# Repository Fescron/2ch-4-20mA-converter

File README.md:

# 2ch-4-20mA-converter

<br/>

This board converts two *4 - 20 mA* signals to a voltage using a `LMP8640` *Current Shunt Monitor* from *Texas Instruments*. To provide power to the *4 - 20 mA* sensors a `TEC2-0913` 2W 15V Isolated DC-DC converter is used from *Traco Power*. Quick-connect terminals from *Phoenix Contact* are also used.

To allow for extensive testing three separate GND nets/planes and a lot of test points are used. They can be connected together using jumpers if necessary. The power supply can also be disabled and fully disconnected from the sensors using a jumper as well (wich can also be used to measure the in-line current given to the whole sensor circuit).

- Click [here](hardware/2ch-4-20mA/2ch-4-20mA.pdf) to go to the **schematic**.

<br/>

 &nbsp; &nbsp; &nbsp; &nbsp; &nbsp; 

<br/>

## LMP8640 vs INA196

A lot of designs still use the `INA196` *Current Shunt Monitor* from *Texas Instruments*. In the picture below is a comparison between the `LMP8640` and the `INA196`. No real disadvantage was found to not use the `LMP8640`.

<br/>

<br/>

## BOM

| Component    | Value                | Footprint     | Other                                       | Ordering                                                                                                                                    |
| ------------ | -------------------- | ------------- | ------------------------------------------- | ------------------------------------------------------------------------------------------------------------------------------------------- |
| U1, U2       | LMP8640              | SOT-23-Thin-6 | Texas Instruments Current Shunt Monitor     | [Mouser.be](https://www.mouser.be/ProductDetail/Texas-Instruments/LMP8640MK-T-NOPB?qs=sGAEpiMZZMvEn2pkGav3bPb6jlX9oNVbBBSIeXfzDzM%3D)                     |
| U3           | TEC2-0913            | SIP-8         | Traco Power 2W 15V Isolated DC-DC converter | [Mouser.be](https://www.mouser.be/ProductDetail/TRACO-Power/TEC-2-0913?qs=sGAEpiMZZMvGsmoEFRKS8Koqt8Pjkl39l4aaKfuLyMgVYp%252Bicpvd3A%3D%3D) |
| C1, C2       | 100 nF = 0,1 µF      | 0805          | X7R, 16V, 10%                               | [Mouser.be](https://www.mouser.be/ProductDetail/Yageo/CC0805KRX7R7BB104?qs=sGAEpiMZZMs0AnBnWHyRQMMzfhmH8IQX2eB5GrOHrwc%3D)                  |
| R1, R2       | 6,2 Ω                | 0805          | 0,1%                                        | [Mouser.be](https://www.mouser.be/ProductDetail/TE-Connectivity-Neohm/CPF0805B6R2E1?qs=sGAEpiMZZMu61qfTUdNhGxAfPTOoMd3Mys3VDWDGxkc%3D)      |
| R1, R2 (alt) | 4,99 Ω               | 0805          | 0,1%                                        | [Mouser.be](https://www.mouser.be/ProductDetail/TE-Connectivity-Neohm/CPF0805B4R99E1?qs=sGAEpiMZZMu61qfTUdNhGxAfPTOoMd3MWO8ubRKmtsI%3D)     |
| J1, J2       | PTSA_1,5/_2-3,5-Z_BK | Pitch: 3,5 mm | 2 contacts @ 45° (20-16 AWG), 250V 2A       | [Mouser.be](https://www.mouser.be/ProductDetail/Phoenix-Contact/1751765?qs=sGAEpiMZZMvZTcaMAxB2AOnzhHajZlLEGRULH%2FxUGnk%3D)                |

<br/>

## UPDATE 03/2020 - 1 CH board without power supply

To better conduct tests with the `LMP8640` chip a simple 1-CH board was layed out without a power supply and etched on a single sided board.

- Click [here](hardware/1ch-4-20mA/Plots/1ch-4-20mA.pdf) to go to the **schematic**.
- Click [here](hardware/1ch-4-20mA/Plots/1ch-4-20mA-F_Cu.pdf) to go to the **board layout** (mirrored).

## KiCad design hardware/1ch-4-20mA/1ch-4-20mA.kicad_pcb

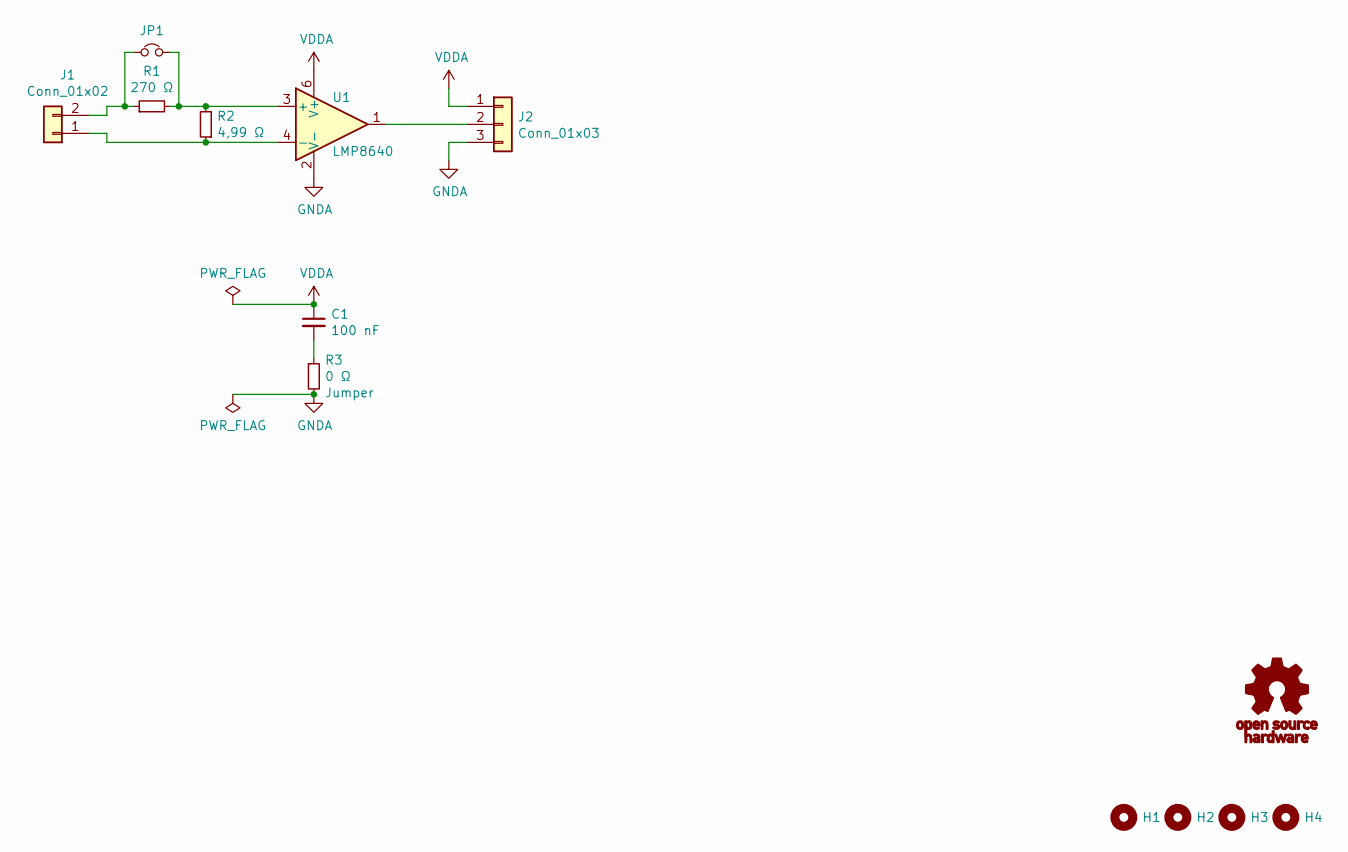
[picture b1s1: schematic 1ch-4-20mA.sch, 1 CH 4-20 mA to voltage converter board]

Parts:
C1: 100 nF; C_0805_2012Metric_Pad1.15x1.40mm_HandSolder
G1: Symbol_OSHW-Logo_11.4x12mm; OSHW-Logo_5.7x6mm_SolderMask
H1, H2, H3, H4: MountingHole; MountingHole_3.2mm_M3
J1: Conn_01x02; PhoenixContact_PTSA_1,5_2-G-3,5_1x02_P3.50mm_Angled
J2: Conn_01x03; PinHeader_1x03_P2.54mm_Vertical_SMD_Pin1Right
JP1: Jumper_NC_Small; PinHeader_1x02_P2.54mm_Vertical_SMD_Pin1Left
R1: 270 Ω; R_0805_2012Metric_Pad1.15x1.40mm_HandSolder
R2: 4,99 Ω; R_0805_2012Metric_Pad1.15x1.40mm_HandSolder
R3: 0 Ω; R_0805_2012Metric_Pad1.15x1.40mm_HandSolder
U1: LMP8640; SOT-23-6_Handsoldering

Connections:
GNDA: J2.3, R3.2, U1.2 (V-)
unnamed: C1.2, R3.1
unnamed: J1.1, R2.1, U1.4 (-)
unnamed: J1.2, JP1.1, R1.1
unnamed: J2.2, U1.1
unnamed: JP1.2, R1.2, R2.2, U1.3 (+)
VDDA: C1.1, J2.1, U1.6 (V+)

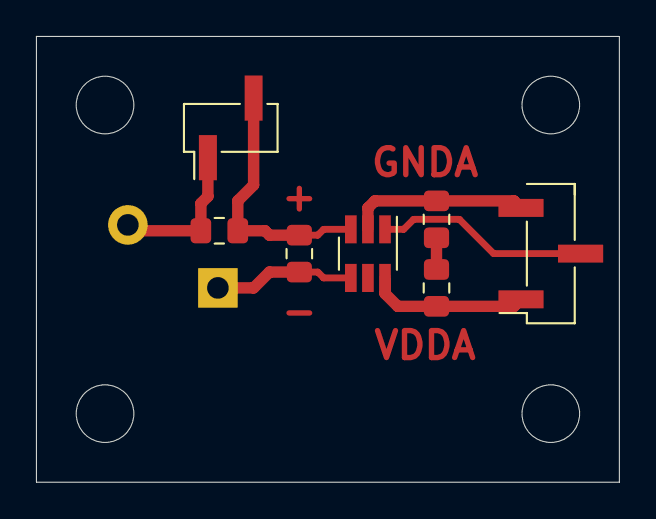
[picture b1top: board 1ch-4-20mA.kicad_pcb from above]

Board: 2 copper layers, 32.4 x 24.8 mm, 13 parts (1 on the bottom side), 7 nets.

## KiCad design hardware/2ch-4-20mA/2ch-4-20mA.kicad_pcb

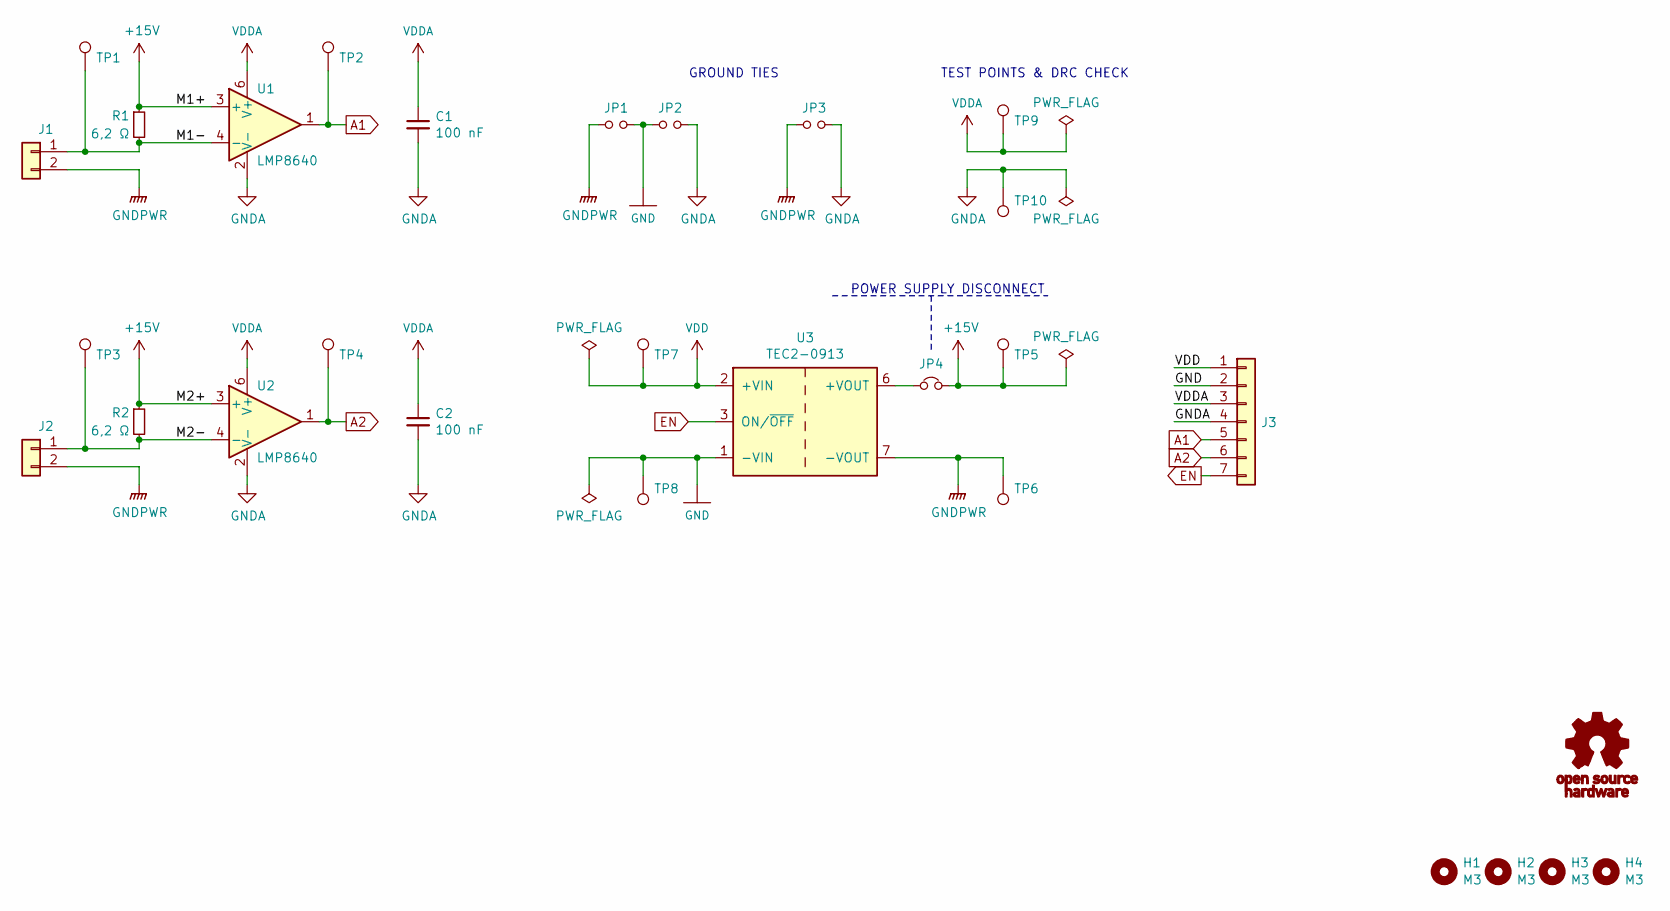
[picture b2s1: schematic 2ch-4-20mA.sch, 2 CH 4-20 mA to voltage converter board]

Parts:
C1, C2: 100 nF; C_0805_2012Metric_Pad1.15x1.40mm_HandSolder
G1: OSHW-EEVBLOG-SPFMDBC-10mm; OSHW-Logo_5.7x6mm_SolderMask
H1, H2, H3, H4: M3; MountingHole_3.2mm_M3
J1, J2: Conn_01x02; PhoenixContact_PTSA_1,5_2-G-3,5_1x02_P3.50mm_Angled
J3: Conn_01x07; PinHeader_1x07_P2.54mm_Vertical
JP1, JP2, JP3: Jumper_NO_Small; PinHeader_1x02_P2.54mm_Vertical
JP4: Jumper_NC_Small; PinHeader_1x02_P2.54mm_Vertical
R1, R2: 6,2 Ω; R_0805_2012Metric_Pad1.15x1.40mm_HandSolder
TP1, TP2, TP3, TP4, TP5, TP6, TP7, TP8, TP9, TP10: TestPoint; TestPoint_THTPad_D2.0mm_Drill1.0mm
U1, U2: LMP8640; SOT-23-6_Handsoldering
U3: TEC2-0913; SIP-8 TEC2-0913

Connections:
+15V: JP4.2, R1.1, R2.1, TP5.1, U1.3 (+), U2.3 (+)
/M1-: J1.1, R1.2, TP1.1, U1.4 (-)
/M2-: J2.1, R2.2, TP3.1, U2.4 (-)
A1: J3.5, TP2.1, U1.1
A2: J3.6, TP4.1, U2.1
EN: J3.7, U3.3 (ON/~OFF)
GND: J3.2, JP1.2, JP2.1, TP8.1, U3.1 (-VIN)
GNDA: C1.2, C2.2, J3.4, JP2.2, JP3.2, TP10.1, U1.2 (V-), U2.2 (V-)
GNDPWR: J1.2, J2.2, JP1.1, JP3.1, TP6.1, U3.7 (-VOUT)
unnamed: JP4.1, U3.6 (+VOUT)
VDD: J3.1, TP7.1, U3.2 (+VIN)
VDDA: C1.1, C2.1, J3.3, TP9.1, U1.6 (V+), U2.6 (V+)

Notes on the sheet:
GROUND TIES
TEST POINTS & DRC CHECK
POWER SUPPLY DISCONNECT

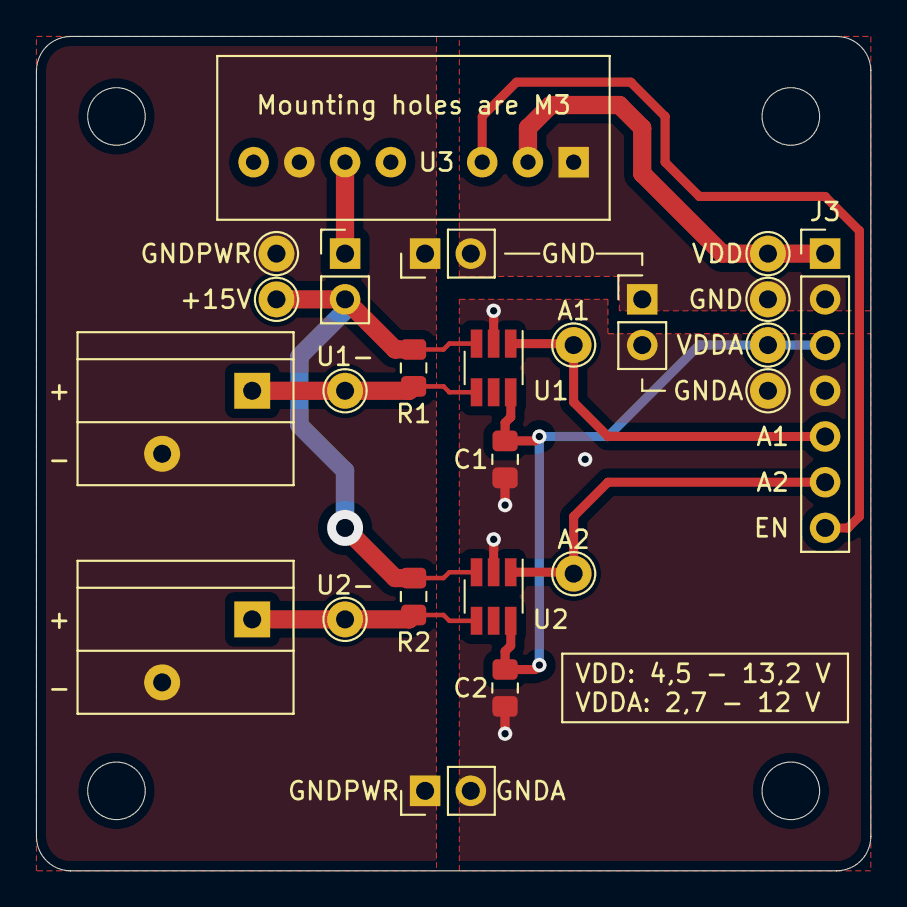
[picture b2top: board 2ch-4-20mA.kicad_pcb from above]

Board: 2 copper layers, 46.4 x 46.4 mm, 29 parts (0 on the bottom side), 12 nets.

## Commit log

2019-11-25 Upload files
2019-11-25 Update PRODUCT.md title
2019-11-25 Updated schematic with selectable text
2019-11-26 Updated PCB with new OSHW logo
2019-11-26 Added new OSHW logo's
2019-12-03 Updated readme with note about wrong footprint
2019-12-10 Updated header footprint
2019-12-10 Updated pictures
2020-01-07 Updated BOM with correct gain for current shunt monitor
2020-03-16 Added info about 1CH board
2020-03-16 Moved licence files
2020-03-16 Added 1CH single layer breakout board
2021-08-30 Added PDF files
2021-08-30 Small info changes

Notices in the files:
README.md:
License: CERN OHL v.1.2
hardware/2ch-4-20mA/2ch-4-20mA.kicad_pcb:
Licensed under CERN OHL v.1.2
